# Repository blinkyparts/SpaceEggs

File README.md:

# Space Egg – Illuminated DIY Soldering Kit

The **Space Egg** is a fun and beginner-friendly **soldering kit** combined with **3D-printed components**. It features an interactive mechanism where turning the egg aligns a **magnetic switch (reed switch)** with a **magnet**, powering on the three **RGB LEDs**. This creates a stunning light effect inside the egg and the flame underneath the rocket-shaped egg cup.

This fantastic kit was created in collaboration with **Olaf Emcke**.

## Where to Buy?
You can purchase the Space Egg kit in our online store:

➡️ [Buy the Space Egg Kit Here](https://shop.blinkyparts.com/de/Space-Eggs-Leuchtender-Loetbausatz-mit-3D-gedrucktem-Raketen-Eierbecher/blink23128)

## Features
- **Easy soldering kit** – Perfect for beginners
- **Innovative mechanism** – Turns on by simply rotating the egg
- **RGB LEDs for stunning lighting effects**
- **Great Easter gift** – Decorative and interactive
- **Sustainable materials** – 3D-printed parts made from recycled PLA

## Included in the Kit
| Quantity | Description |
|:--------:|:-----------|
| 3 | RGB LEDs (5 mm) |
| 1 | LED Spacer |
| 1 | Egg (two parts) |
| 1 | Rocket Egg Cup (3D-printed, optional) |
| 1 | Flame Base (3D-printed, optional) |
| 1 | Reed Switch (Magnetic Switch) |
| 1 | CR2032 Battery Holder |
| 1 | CR2032 Battery (not included) |
| 1 | 8x2 mm Neodymium Magnet |
| 1 | Space Eggs PCB |

## Assembly Instructions
For assembly, you will need:
- **Superglue or hot glue** for fixing parts
- **5 mm drill bit** for minor adjustments

A detailed **step-by-step guide** is available in the Wiki and GitHub repository.

## 3D Printing Files
The **3D print files** for the rocket egg cup and flame base can be found here:
➡️ [Download 3D Print Files](#) *(Insert Printables, Thingiverse, or GitHub link)*

## License
This project is licensed under **CC-BY-SA 4.0** - Olaf Emke and Timo Schindler

**Happy Soldering! 🚀🥚**

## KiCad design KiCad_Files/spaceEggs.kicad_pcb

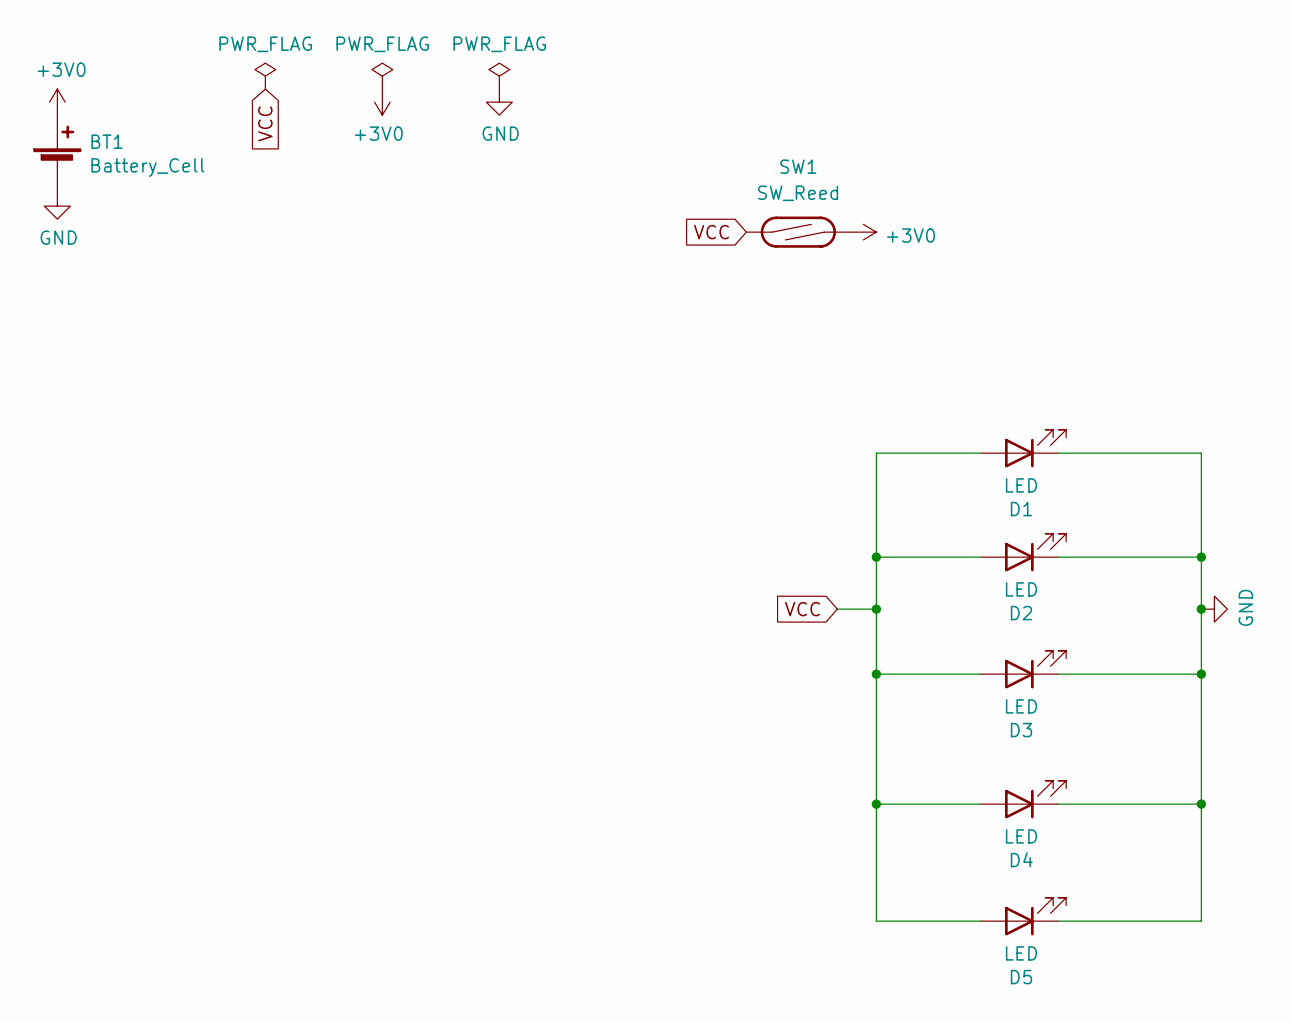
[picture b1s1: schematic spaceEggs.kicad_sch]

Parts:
BT1: Battery_Cell; BatteryHolder_CR2032_schwarz
D1, D2, D3: LED; LED_D5.0mm_PLUS-Symbol
D4, D5: LED; 5mm_SMD-Pad
SW1: SW_Reed; R_Axial_DIN0309_L9.0mm_D3.2mm_P20.32mm_Horizontal

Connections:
+3V0: BT1.1 (+), SW1.2
GND: BT1.2 (-), D1.1 (K), D2.1 (K), D3.1 (K), D4.1 (K), D5.1 (K)
VCC: D1.2 (A), D2.2 (A), D3.2 (A), D4.2 (A), D5.2 (A), SW1.1

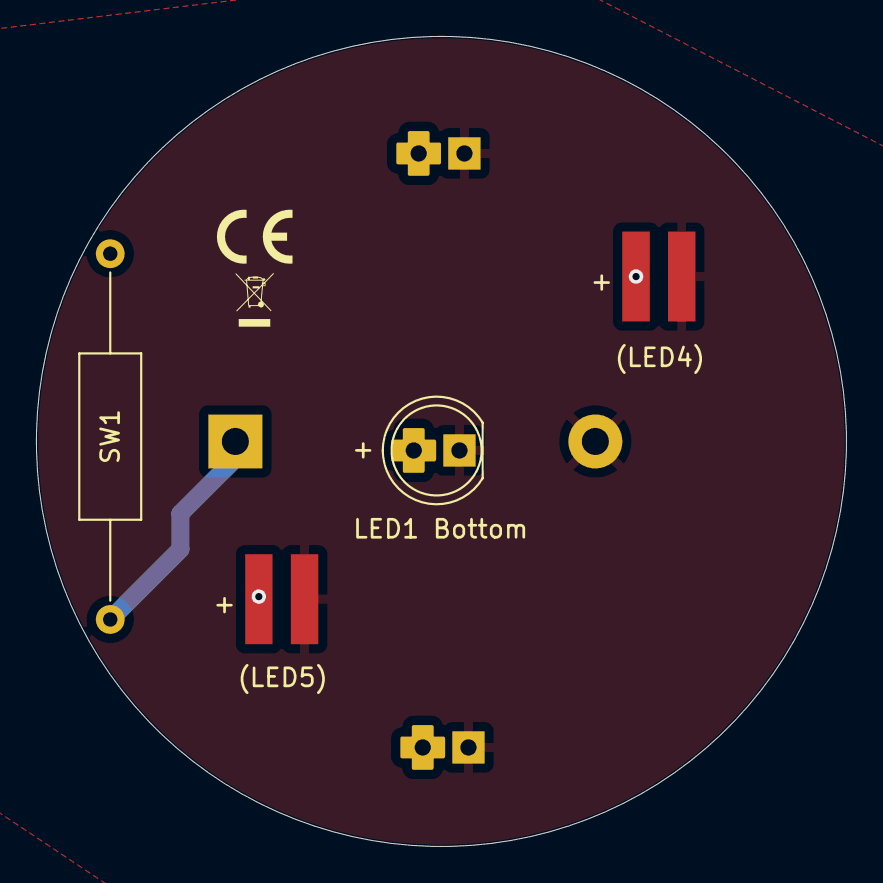
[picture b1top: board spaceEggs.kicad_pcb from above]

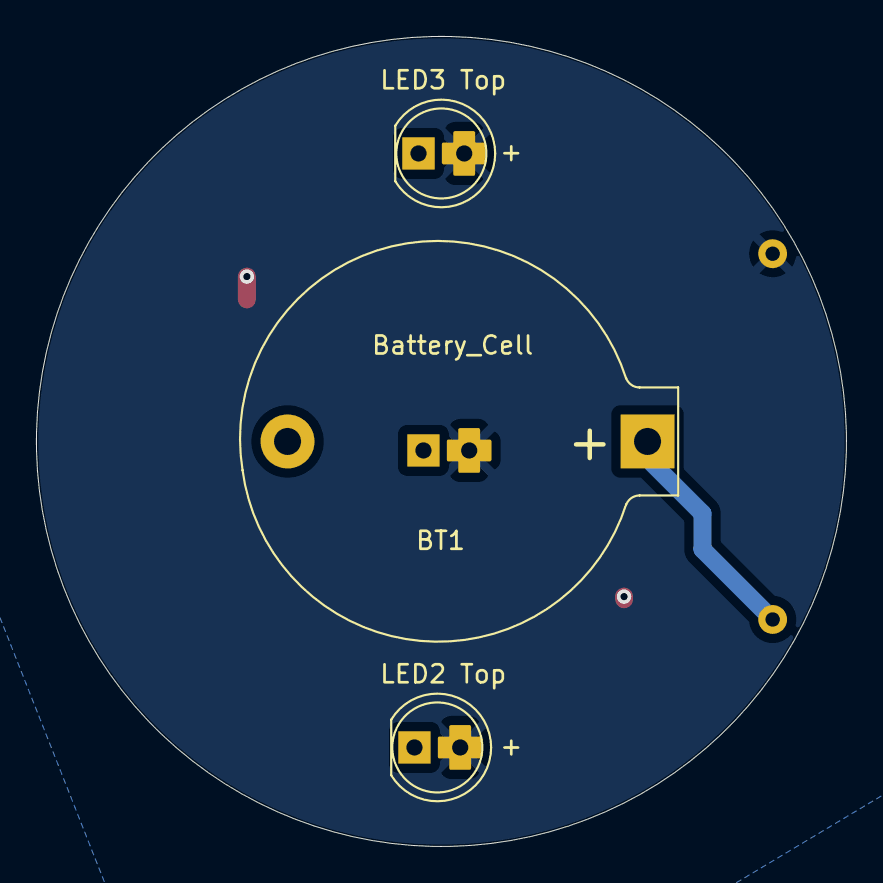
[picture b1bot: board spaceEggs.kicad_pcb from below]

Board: 2 copper layers, 45.0 x 45.0 mm, 9 parts (3 on the bottom side), 3 nets.

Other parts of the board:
ce-symbol_mask_3mm: G***; ce-icon_3mm
weee-symbol_mask_3mm: G***; weee-icon_3mm

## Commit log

2025-03-05 added standard .gitignore
2025-03-05 added standard Licence file
2025-03-05 added some images and led svg
2025-03-05 added kicad files for version 1.0 and 1.1
2025-03-05 added CE & Weee Icon
2025-03-05 closing Issue #2
2025-03-06 added readme
2025-03-06 some images
2025-03-06 some changes and added bom
